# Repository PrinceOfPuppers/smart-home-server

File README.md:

# Smart Home Server
> A Full Smart Home System and Associated IOT Devices

- [DEVICES](#devices)
- [INSTALLATION](#installation)
  * [INSTRUCTIONS](#instructions)
- [ABOUT](#about)
  * [JOBS AND MACROS](#jobs-and-macros)
  * [DATASOURCES](#datasources)
- [PAGES](#pages)
  * [DASHBOARD](#dashboard)
  * [NOTE](#note)
  * [LCD](#lcd)
  * [REMOTE](#remote)
  * [SCHEDULE](#schedule)
  * [TRIGGER](#trigger)
  * [MACRO](#macro)
  * [GRAPH](#graph)

# DEVICES
Each device has its own `README`. Click the links to read more.

[ESP32 Air Quality Station](devices/esp32-air-quality-station/README.md) and [ESP Dashboard](devices/esp-dashboard/README.md):

<br clear="left"/>
<br clear="left"/>

[Main Case](devices/main-case/README.md) and [Arduino Blinds Controller](devices/arduino-blinds/README.md):

<br clear="left"/>
<br clear="left"/>

[Atmega16u2 Monitor](devices/atmega16u2-monitor/README.md)

<br clear="left"/>
<br clear="left"/>

[ESP Weather Station](devices/esp-weather-station/README.md) and [Arduino Modular Controller](devices/arduino-modular-controller/README.md):

<br clear="left"/>
<br clear="left"/>

# INSTALLATION
This section covers the installation of the central smart-home-server (hereto called "the server"). For a full parts list and physical assembly see: [Main Case Readme.md](devices/main-case/README.md)

The server runs RaspberryPi OS Lite, it has only been tested on a RaspberryPi 4B. I'd recommend using rpi-imager for creating the image as it lets you setup WiFi, SSH, etc, for an easier experience.

### Instructions
1) Flash an SD card with RaspberryPi OS Lite using rpi-imager, edit the settings to configure your user, WiFi, ssh, and other settings

2) Boot up the server and let it connect to wifi, in your router set a static IP address for the server

3) Reboot the server and connect to it over ssh

4) Ensure a USB stick is connected to the Pi and run: 

```
sudo apt install -y git && git clone https://github.com/PrinceOfPuppers/smart-home-server.git && cd smart-home-server && ./install.sh
```

5) The Installer will prompt you to select the usb stick from a list (will likley be the only one), after it is finished the server will be ready to go and accessable at its static ip address.

Note: The installer script enables read only file system, this makes the SD card readonly but still allows writing to the USB stick. You can disable this and re-enable it using `sudo raspi-config`

# ABOUT
The smart-home-server (hereto called "the server") is a device for collecting data and controlling IOT devices (hereto called "devices"). The server runs a full web interface for easy control on mobile or desktop.

The server's functionality is best understood through two categories, [Jobs and Macros](#jobs-and-macros) and [Datasources](#datasources).

## Jobs and Macros
Jobs are things the server can do, they include:
- Transmitting RF signals (for controlling RF outlets and relays)
- Sending HTTP requests
- Updating remote LCD Dashboard formats (see LCDs page)
- Running Job Macros
- Updating the server
- And more

Jobs can be organized into macros and setup to trigger in on RF signals, button presses on the server's case, or manually through the web page.

Jobs and macros can also be run using a scheduler (i.e. turn off the lights at 11pm) or can be triggered on conditions (i.e. turn on the humidifier whenever relative humidity is below 35%). See the [Schedule](#schedule) and [Trigger](#trigger) pages for more details.

Macros can also include delays and other macros.

### Example
Here is an example of a simple nighttime macro:

<br clear="left"/>
<br clear="left"/>

This macro turns off all the lights, turns off a loud air filter in the bedroom, waits for 8h30min, prevents you from oversleeping by turning on the bedroom light, and then turns everything in the bedroom off after 30 more minutes.

This macro could be hooked up to an RF button outside the bedroom to be run without having to open the web app (how I do it).

The macros like bedroom on/off would be replaced with single RF switching jobs, i.e.) `press bedroom ch: 1 on`, for the example macros where used so they could be labeled.

## Datasources
The server collects data from `datasources` with a set polling period. The data can then be used to:
- [Trigger](#trigger) server [Jobs](#jobs-and-macros) on conditions
- Displayed on the [Dashboard](#dashboard)
- Create [Graphs](#graph)
- Displayed on local and remote [LCDs](#lcd)

Examples of each Application:

<br clear="left"/>
<br clear="left"/>

<br clear="left"/>
<br clear="left"/>

Datasources can be added and changed on the `Datasources` tab if they fit into one of the existing types:
- `Forex`: currency converstion
- `Clock`: tells time
- `AQ`: air quality, temprature and humidity station
- `TempHumid`: temprature and humidity station
- `WeatherImage`: current weather with ascii art image
- `WeatherCurrent`: current weather simple representation
- `Forcast`: long term forcast chart
- `Errors`: log of errors in the smart home
- `JobLog`: log of run jobs
- `RfLog`: log of rf rx/tx
- `Version`: smart home version

New Datasource Form (left). Edit existing Datasource Form (right):

<br clear="left"/>
<br clear="left"/>

Each Datasource can be displayed in the Dashboard and provides values that can be consumed by Job Triggers, Graphs and LCDs

New types of Datasources can be added [here](smart_home_server/data_sources/datasourceTypes.py), by:
1) Creating a new subclass of `Datasource` (use an existing one as a base), Any required arguments should be annotated so they appear correctly in the `Datasource` form
2) Adding a `local` function which returns `{ 'str': '...', 'data':{...} }` where `str` is shown in dashboard and `data` contains the values used by triggers, graphs and etc (this function is polled to get the data).
3) Adding a `values` property which specifies what fields in `data` are relevant and what they should be called
4) Set a sane default polling period, although this is editable in the datasource form

# Pages

## Dashboard
A page for displaying desired datasources in an easy to read way, clicking on the name tag will refresh its information. Each datasource can be customized with buttons to hide its contents, colored name tags, buttons to make HTTP requests, and more.

<br clear="left"/>
<br clear="left"/>

## Note
A page to create, display and edit notes.

<br clear="left"/>
<br clear="left"/>

## LCD
A page to add and update local and [remote LCD](devices/esp-dashboard/README.md) dashboards.

LCDs display formatted text containing datasources, i.e. `{clock} 123` will be replaced with `02:03 PM 123` and will be updated every minute when the `{clock}` changes. This format is set on the LCD page, a list of all formats is provided under `Cheat Sheet`. Numbers can be rounded like so: `{temp:.0f}` for 0 decimal places or `{temp:.1f}` for 1 decimal place.

Each LCD has its own number (0 for local and 1 or more for remote), upon power up the LCDs will reach out to the server to connect, after which the server will send updates whenever the text changes.

<br clear="left"/>
<br clear="left"/>

## Remote
A page for using, adding and editing RF remotes. The server contains an RF receiver to copy existing remotes which can then hook into the server's [job system](#jobs-and-macros), in addition to directly using the copied remote from this page.

Each remote can be named, and additional buttons can be added using the forms at the bottom of the page.

<br clear="left"/>
<br clear="left"/>

## Schedule
A page for triggering [jobs and macros](#jobs-and-macros) repeatedly on a schedule. The server can be setup to run a job on an interval or at a specific time every day or week, for example turn on the Christmas lights at 5pm every day and turn them off at 5am every day.

<br clear="left"/>
<br clear="left"/>

## Trigger
A page for triggering [jobs and macros](#jobs-and-macros) on conditions involving [datasources](#dataSources). The server can be setup to run a job whenever a condition is met, for example whenever humidity is over 30%. comparisons can be made between two datasources as well, for example if you have 2 temperature sensors in different rooms, you can trigger a fan to turn on if room A temp is less than room B temp.

Note the condition is denounced, so it will only trigger once until the condition is no longer met. Using the humidity example, going below 30% will trigger the condition, but it will not trigger again until humidity goes above 30% and then below 30% again. This is to prevent spamming.

<br clear="left"/>
<br clear="left"/>

## Macro
A page for combining [jobs (and macros) into macros](#jobs-and-macros), macros can include jobs, delays and other macros to allow the easy triggering of complex tasks manually, on schedules or using the trigger system. See the [jobs and macro section](#jobs-and-macros) for examples.

<br clear="left"/>
<br clear="left"/>

## Graph
A page for creating plots of datasources over time. New graphs can be created by selecting a datasource, a color, and a time interval to plot over. All the plots are created server side and served as an image so they can be easily saved. Clicking on the plots name or refreshing the page will update it.

<br clear="left"/>
<br clear="left"/>

If an [Atmega16u2 Monitor](./devices/atmega16u2-monitor/README.md) is connected, you can press the `Monitor` button to push it to the screen where it will be updated whenever new data is added.

<br clear="left"/>
<br clear="left"/>

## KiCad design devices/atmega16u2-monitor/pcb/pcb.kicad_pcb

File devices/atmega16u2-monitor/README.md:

# Atmega16u2 Monitor
> An OLED and LCD USB Device for Displaying Graphs from smart-home-server

<br clear="left"/>
<br clear="left"/>

- [ABOUT](#about)
- [CREATION](#creation)
- [OPERATION](#operation)
- [TROUBLESHOOTING](#TROUBLESHOOTING)

# ABOUT
This device is a plug and play graph monitor for smart-home-server's data sources. When plugged in it will automatically connect to the server and start displaying whichever graph is selected in the UI (by pressing the `Monitor` button shown below). The image is updated whenever new data is added to the graph.

<br clear="left"/>
<br clear="left"/>

The device features a custom PCB built around the Atmega16u2

<br clear="left"/>
<br clear="left"/>

# CREATION

### PCB Creation and Assembly

JLCPCB was used for PCB creation and the majority of PCB assembly, files are provided in `./pcb/product`, these can be directly dropped into JLCPCB. The only things hand soldered are the USB connector, oscillator and debug header pin J5 (which is optional).

The schematic, PCB and components used can be edited in Kicad using file `./pcb/pcb.kicad_pro`, the JLCPCB files come from a plugin called `fabrication toolkit`.

<br clear="left"/>
<br clear="left"/>

### Display

I have tested with waveshare's OLED 1.5 inch display as well as their 1.8 inch LCD display. The type of display and its size are selected in `./firmware/config.h`. Wider displays may require increasing the number of `CHUNKS_PER_LINE` due to RAM limitations of the Atmega16u2.

The display's pins slot directly into the 8 pin port on the board. The pinout is `VCC, GND, DIN, CLK, CS, DC, RST, BL`. For OLED displays, `BL` is not used.

### Physical Assembly

3D printable cases for the 1.5 inch OLED and 1.8 inch LCD are provided under `./case/*.stl` as well as the openscad sources under `./case/*.scad`. Additional sizes can be added by editing `screenWidth` and `screenHeight` in the `.scad` files. Separate files exist for the OLED and LCD variants due to different pin locations.

The display is secured to the board using m2.5 standoffs as shown below, Note the OLED variant only uses one standoff due to its different form factor.

<br clear="left"/>
<br clear="left"/>

The screen is secured to the case using m2.5 screws, which screw into the standoffs (where present) or nuts. Nuts can also be used as spacers between the screen and case if desired.

<br clear="left"/>
<br clear="left"/>

### Firmware and Fuses

Fuses must be set on the Atmega16u2 for it to use the crystal resonator, these can be set by running:
```
./fuses.sh
```

The fuses should be `efuse: 0xF4`, `hfuse: 0xD9`, `lfuse 0xFF`. They can then be checked with:
```
./check_fuses.sh.sh
```

Fuses only need to be set once per device. Firmware can be uploaded by running the following.
```
./build.sh
```

The build relies [Hoodloader2](https://github.com/NicoHood/HoodLoader2) and [Hid Project](https://github.com/NicoHood/HID). The former makes the Atmega16u2 compatible with Arduino's build system and the latter is a library which manages the RawHID interface.

### UDEV and Testing
A UDEV rule must be added for Linux to know what to do with the USB device, smart-home-server does this automatically when installed. For local testing, a UDEV rule can be added by running the following script (once).
```
./udev.sh
```

After this, when the device is plugged in, it can be tested using the python script shown below. It will show a test graph and cycle through various line colors every 5 seconds.
```
python3 ./test.py
```

### Debugging
Uncomment `#define DEBUG_ENABLED` in `./firmware/config.h` and connect pin `J5` to the `RX` pin of a serial interface (I use a UART to USB adapter). This will give you serial debugging, several debug prints already exist in the code. Be mindful, `debug("test string");` stores the string `"test string"` in global RAM which can run out quickly on the Atmega16u2 and cause stack overflows. To give you more overhead, debug mode lowers the chunk size of the screen buffer.

Several macros exist for debug printing: `debug(x), debugln(x), debugS(x), debugSln(x)`. The `ln` variants print a newline after `x`, the `S` variants coerce `x` to a string before printing.

A debug LED is hooked up to pin `D6` (also known as pin `19`). It's free to use for debugging and is not accessed by anything else in the firmware.

# Operation
Once the device is assembled it can be plugged into the server, you can then select a graph to push to the screen. Only one graph can be shown at a time, the selected graph will have a grayed out button saying `Monitoring`, other graphs will have a colored button that says `Monitor`.

<br clear="left"/>
<br clear="left"/>

The graph updates whenever there is new data to display, the x axis is time relative to when it was last updated with time units displayed at the top.

<br clear="left"/>
<br clear="left"/>

# TROUBLESHOOTING

### USB not Connecting
The device should appear as a raw hid device under `/dev`, unplug it and run `ls /dev/hid*`, plug it back in and wait for a second, then run `ls /dev/hid*` again, a new device should appear.

You can also run the following command to check for USB add, bind, unbind and remove events.
```
udevadm monitor
```

If no device appears, it could be:
- device isn't plugged in properly
- firmware isn't flashed
- fuses aren't set correctly
- UDEV rule wasn't copied
- UDEV rules weren't reloaded
- hardware issues

Ensure the hardware is working using either serial debugging, or by blinking the debug led. You can also sniff USB traffic by connecting to the middle to pins on the USB adapter.

### Freezing
The device can freeze if undervolted (happens below 4v), some cheap USB splitters can cause this, if it occurs, try connecting directly to a USB port on your computer. The smart-home's USB ports have no issues. Freezing typically happens mid screen update.

### Slow Updating and USB Disconnects
Typically happens when the fuses are set incorrectly, check them with `./check_fuses.sh`. If the fuses are set properly check if `python3 ./test.py` changes color every 5 seconds. If so the timing is fine. If not, try re-running `./fuses.sh` (I've had say it succeeded, but the fuses remained unset). During normal operation, update speed is limited by chunk size which can be adjusted in `./firmware/config.h` by changing `#define CHUNKS_PER_LINE`. Fewer chunks is faster but uses more RAM and can lead to stack overflows.

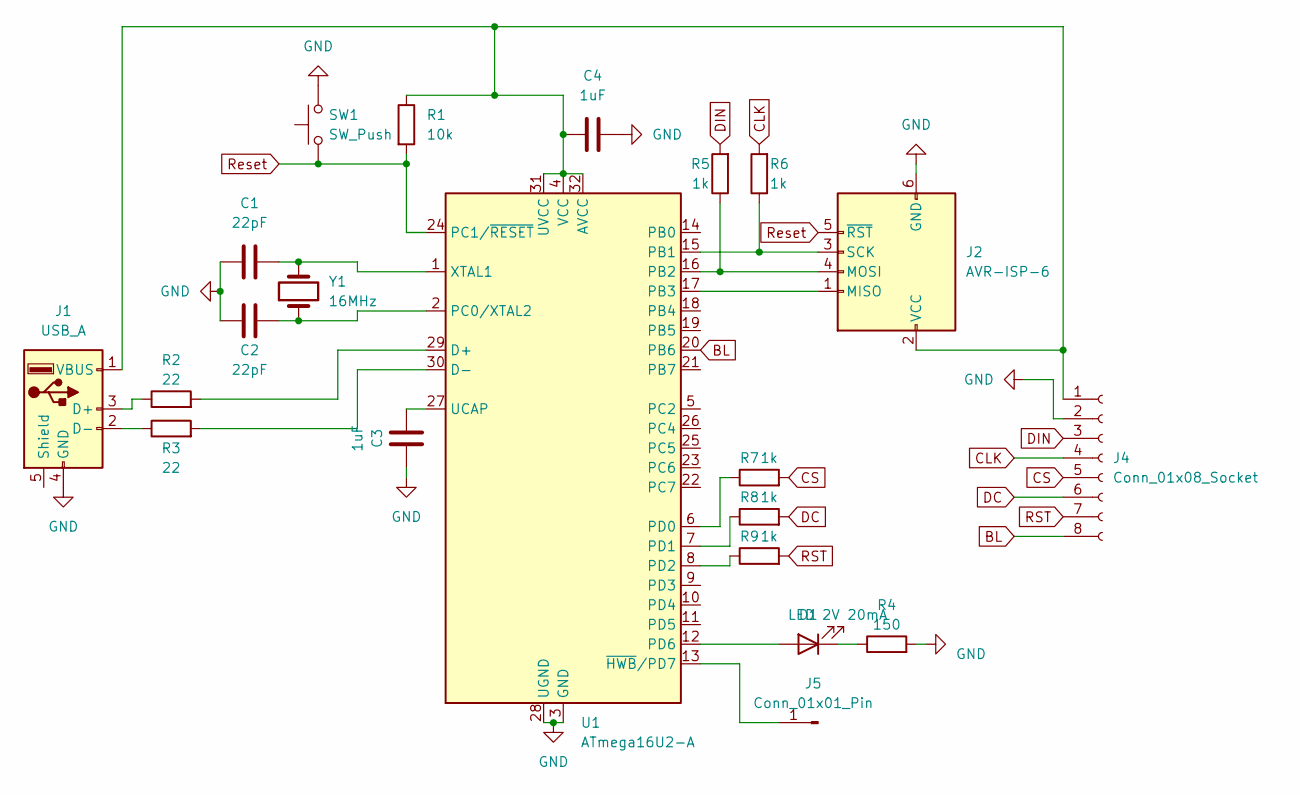
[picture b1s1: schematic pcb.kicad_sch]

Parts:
C1, C2: 22pF; C_0603_1608Metric
C3, C4: 1uF; C_0603_1608Metric
D1: LED 2V 20mA; LED_0603_1608Metric
J1: USB_A; USB_A_CNCTech_1001-011-01101_Horizontal
J2: AVR-ISP-6; PinHeader_2x03_P2.54mm_Horizontal
J4: Conn_01x08_Socket; PinSocket_1x08_P2.54mm_Vertical
J5: Conn_01x01_Pin; PinHeader_1x01_P2.54mm_Horizontal
R1: 10k; R_0603_1608Metric
R2, R3: 22; R_0603_1608Metric
R4: 150; R_0603_1608Metric
R5, R6, R7, R8, R9: 1k; R_0603_1608Metric
SW1: SW_Push; SW_Tactile_SPST_NO_Straight_CK_PTS636Sx25SMTRLFS
U1: ATmega16U2-A; TQFP-32_7x7mm_P0.8mm
Y1: 16MHz; Crystal_HC49-4H_Vertical

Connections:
BL: J4.8, U1.20 (PB6)
CLK: J4.4, R6.2
CS: J4.5, R7.2
DC: J4.6, R8.2
DIN: J4.3, R5.2
GND: C1.1, C2.1, C3.2, C4.2, J1.4 (GND), J2.6 (GND), J4.2, R4.2, SW1.2, U1.3 (GND), U1.28 (UGND)
unnamed: D1.2 (A), U1.12 (PD6)
unnamed: D1.1 (K), R4.1
unnamed: J1.3 (D+), R2.1
unnamed: J1.2 (D-), R3.1
unnamed: C4.1, J1.1 (VBUS), J2.2 (VCC), J4.1, R1.1, U1.4 (VCC), U1.31 (UVCC), U1.32 (AVCC)
unnamed: J2.1 (MISO), U1.17 (PB3)
unnamed: J2.4 (MOSI), R5.1, U1.16 (PB2)
unnamed: J2.3 (SCK), R6.1, U1.15 (PB1)
unnamed: J5.1, U1.13 (~HWB/PD7)
unnamed: R2.2, U1.29 (D+)
unnamed: R3.2, U1.30 (D-)
unnamed: C2.2, U1.2 (PC0/XTAL2), Y1.1
unnamed: R7.1, U1.6 (PD0)
unnamed: R8.1, U1.7 (PD1)
unnamed: R9.1, U1.8 (PD2)
unnamed: C3.1, U1.27 (UCAP)
unnamed: C1.2, U1.1 (XTAL1), Y1.2
RST: J4.7, R9.2
Reset: J2.5 (~RST), R1.2, SW1.1, U1.24 (PC1/~RESET)

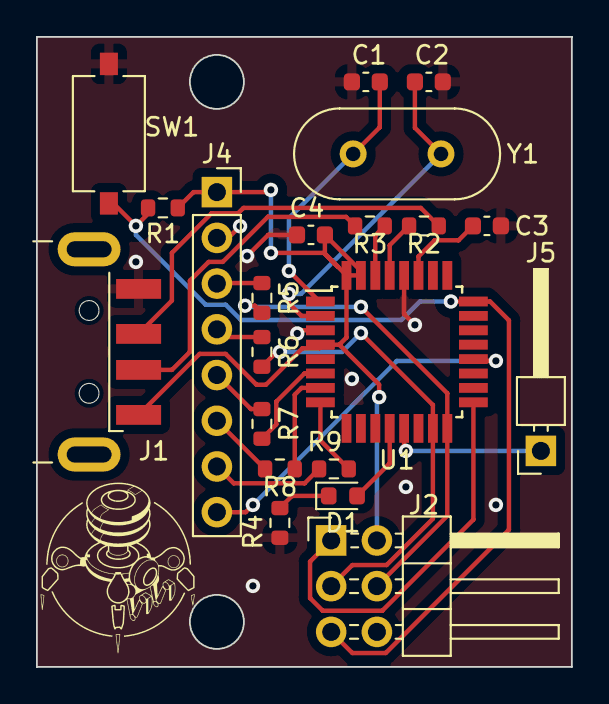
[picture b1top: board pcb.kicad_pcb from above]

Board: 2 copper layers, 29.7 x 35.0 mm, 21 parts (0 on the bottom side), 25 nets.

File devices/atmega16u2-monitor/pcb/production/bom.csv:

Designator,Footprint,Quantity,Value,LCSC Part #
"C1, C2",0603,2,22pF,
"C3, C4",0603,2,1uF,
D1,0603,1,LED 2V 20mA,
J1,USB_A_CNCTech_1001-011-01101_Horizontal,1,USB_A,
J2,PinHeader_2x03_P2.54mm_Horizontal,1,AVR-ISP-6,
J4,PinSocket_1x08_P2.54mm_Vertical,1,Conn_01x08_Socket,
J5,PinHeader_1x01_P2.54mm_Horizontal,1,Conn_01x01_Pin,
R1,0603,1,10k,
"R2, R3",0603,2,22,
R4,0603,1,150,
"R5, R6, R7, R8, R9",0603,5,1k,
SW1,SW_Tactile_SPST_NO_Straight_CK_PTS636Sx25SMTRLFS,1,SW_Push,
U1,TQFP-32_7x7mm_P0.8mm,1,ATmega16U2-A,
Y1,Crystal_HC49-4H_Vertical,1,16MHz,

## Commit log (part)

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2022-11-18 inital commit
2022-11-19 scheduler work
2022-11-19 project restructuring
2022-11-19 api seperation
2022-11-19 bugfixes
2022-11-19 demo site hookup
2022-11-20 rf tranmitter setup
2022-11-20 basic web interface for rf remote
2022-11-21 schedule frontend wip
2022-11-21 schedule frontend bugfixes
2022-11-21 removed hovor on mobile
2022-11-22 bugfixes and layout improvements
2022-11-22 layout changes
2022-11-22 beautification
2022-11-22 more bugfixes
2022-11-22 removed nobr tags, name updating, bugfixes
2022-11-22 small graphical improvements
2022-11-23 api directory structure changes
2022-11-23 additional dashboard elements
2022-11-23 additional sanitization
2022-11-24 lcd wip
2022-11-25 dashboard and lcd improvements
2022-11-25 dht sensor and general improvments
2022-11-25 api changes
2022-11-26 changed data system
2022-11-26 data sources cache
2022-11-27 trigger page wip
2022-11-27 trigger page wip 2
2022-11-27 trigger frontend done
2022-11-28 trigger bugfixes
2022-12-05 job system improvements and change lcd text job
2022-12-05 redirect index to dashboard
2022-12-05 lcd bugfixes
2022-12-06 setup scripts
2022-12-07 deployment bugfixes
2022-12-07 fixed submit form issues
2022-12-09 fixed deployment issues
2022-12-10 workarounds for bugs in wttr.in, moved presser to seperate process
2022-12-10 error system
2022-12-10 code cleanup
2022-12-10 partial lcd update jobs
2022-12-11 inital wip
2022-12-12 websock wip
2022-12-12 websocket robust frontend reconnecting
2022-12-12 fixed more with websockets
2022-12-12 replaced waitress with gevent
2022-12-13 removed websockets for performance reasons
2022-12-13 small fixes
2022-12-13 fixed bug with getCurrentWeather, made polling toggleable in code
2022-12-16 small bugfixes
2022-12-16 auto update on startup
2022-12-16 fixed missing fi in install script
2022-12-16 added missing then to install script
2022-12-18 changes to auto update system
2022-12-18 fixed typo
2022-12-19 dht powercycling
2022-12-19 fixed frontend time string
2022-12-21 better caching system
2022-12-22 version string in dashboard
2022-12-24 fixed bug with pigpiod
2022-12-27 added stacktraces to exceptions
2022-12-27 fixed deadlock in caching on function exception
2022-12-28 added update to install script
2022-12-30 multi remote system
2022-12-30 request timeout
2022-12-31 note system
2022-12-31 macro system inital work
2022-12-31 note newline bugfixes
2023-01-01 reactive buttons
2023-01-01 removed repatition
2023-01-01 macro wip 2
2023-01-01 macro wip 3
2023-01-01 macro wip 4
2023-01-02 macro bugfixes
2023-01-02 improved macro visuals
2023-01-02 visual improvments and removed repititions
2023-01-02 added missing characters to font
2023-01-02 fixed issue with trigger enable/disable system
2023-01-02 dethreaded trigger manager
2023-01-02 added reboot job
2023-01-02 macro renaming and small refactoring
2023-01-02 style improvements
2023-01-02 reboot fixes and style changes
2023-01-03 refactoring
2023-01-03 note refactor
2023-01-03 renamed threads to handlers
2023-01-03 scheduler error system refactor
2023-01-03 made errorhandling and data validation/sanitization more consistant across parts of the api
2023-01-04 added macro to job system
2023-01-04 systemd start after timesync
2023-01-07 after time-sync.target
2023-01-08 skip/cancel macro delay
2023-01-08 removed weather from dashboard due to inaccuracies
2023-01-08 changed order of delay time inputs to hh/mm/ss
2023-01-08 reboot delay timer
2023-01-13 presser process priority
2023-02-06 delayed scheduler loading to account for system time issues on startup
2023-02-24 removing press delay
2023-03-06 api wip
2023-03-08 gui wip
2023-03-08 backend wip
2023-03-08 more frontend wip
2023-03-09 bugfixes and wip
2023-03-09 bugfixes:
2023-03-09 cleanup
2023-03-09 removed deadlock
2023-03-09 preformance improvements
2023-03-09 re added presser thread
2023-03-10 bugfixes and refactoring
2023-03-10 minor graphical tweak and version bump
2023-03-11 software update job
2023-03-14 offset frontend remote channels by 1
2023-03-14 fixed update job
2023-03-14 auto update test
2023-07-08 rf runner thread
2023-07-08 rf macro api
2023-07-09 rf macro frontend work and backend bugfixes
2023-07-09 adjusted rf macro constants
2023-07-10 rf log and hideable elements in dashboard
2023-07-10 dashboard button system and clearable logs
2023-07-10 bumped version number
2023-07-10 minor bugfix
2023-07-10 fixed bug with missing macro id
2023-07-11 more dashboard automation
2023-07-21 renamed
2023-07-23 restructured project
2023-07-23 motion sensor code
2023-07-23 light sensor intial code
2023-07-24 bugfix
2023-08-05 light sensor fixes and debugging
2023-08-07 motion sensor improvement
2023-08-11 potentiometer servo adjustment and field runnable tests
2023-08-11 readme
2023-08-11 Fixed readme format errors
2023-08-11 readme grammer and formatting
2023-08-12 updated servo-invert and servo adjustment range
2023-08-12 updated readme section about servo invert
2023-08-16 tx trigger
2023-08-16 power trigger
2023-08-17 fixed power trigger schematic
2023-11-25 fixed spelling mistake
2023-11-25 fixed issue with return in getBME
2023-11-25 indoor climate rounding
2023-11-25 remote renaming
2023-11-25 macro controls refresh page
2023-11-26 outdoor weather server integration
2023-11-26 ui changes
2023-12-01 made lcd dimensions configurable
2023-12-01 case model
2023-12-02 updated case
2023-12-02 wttrin bugfix
2023-12-02 more wttrin bugfixes
2023-12-03 subscribe manager none error
2023-12-09 updated case model
2023-12-09 added model for weather station case
2023-12-09 indoor weather server added
2023-12-09 added print chamber temp humid station
2023-12-09 fixed issue with caching
2023-12-11 added weather station files
2023-12-11 removed gitignore from subdir
2023-12-11 added devices subdir
2023-12-12 dashboard device inital code
2023-12-14 forcast time indicator
2023-12-23 dashboard case model
2023-12-26 updated dashboard case model
2023-12-28 remote dashboard server code wip
2023-12-29 remote dashboard server code wip 2
2023-12-29 remote dashboard server code wip 3
2023-12-30 remote dashboard api
2023-12-30 inital frontend work for remote dashboard
2023-12-30 remote dashboard frontend wip
2023-12-30 remote dashboard frontend working
2023-12-31 switched over remote dashboard to use TCP instead of UDP
2024-01-02 fix fmt change inducing reconnect
2024-01-02 fixed issue with tcp ports never timing out
2024-01-03 fixed issue with lcd buffer being too small
2024-01-04 lcd backlight toggling
2024-01-04 udp multiple attempts
2024-01-08 added indicator on lcds page for active lcds
2024-01-08 added tcp keepalive, hardware timer watchdog and wifi disconnect handler to esp dashboard
2024-01-10 weather station alternative case
2024-01-10 set esp dashboard hostname
2024-01-10 usb case fix
2024-01-11 added additional weather station
2024-02-04 pms sensor sleep wake cycle
2024-02-05 fixed compile errors
2024-02-05 restart on disconnect
2024-02-05 added data transmission code
2024-02-05 bugfixes and full testing
2024-02-11 s8 calibration and bugfixes
2024-02-12 air quality station case wip
2024-02-13 air quality station case
2024-02-14 air quality station case update
2024-02-14 air quality station bugfixes and docs update
2024-02-14 air quality station images
2024-02-14 air quality station updated readme
2024-02-14 added smart-home-server support
2024-02-15 redesigned error system
2024-02-15 manual error clearing
2024-02-15 added readme for esp-dashboard device
2024-02-15 updated readme for esp-dashboard device
2024-02-17 added readme for esp-weather-station
2024-02-17 reverted max-height to height in readmes
2024-02-18 rounding support in formatter
2024-02-18 bumped lcd api maxLength
2024-02-18 bumped verion number
2024-02-19 inital graphs commit
2024-02-20 graph api
2024-02-20 inital graph integration
2024-02-20 more graph integration
2024-02-20 removed graph names and updating
2024-02-20 graph colors
2024-02-21 made button layout tighter
2024-02-21 fixed small text on macro page
2024-02-21 updated dependancies and version bump
2024-02-21 fixed button color
2024-02-21 additional errors
2024-02-22 created jinja macro for topnav
2024-02-26 readme wip
2024-02-26 bugfixes and ui changes
2024-02-28 more readme wip
2024-02-28 readme first draft
2024-02-28 fixed readme images
2024-02-28 readme spelling fixes
2024-02-29 readme proofreading
2024-03-22 blinds scad files added
2024-03-22 added chain gear model and fixed imports
2024-03-27 mechanical design updates and debug mode
2024-04-12 fixed incorrect clock type bug
2024-04-13 added infield rx programming
2024-04-14 added readme for arduino blinds
2024-04-14 updated main readme
2024-04-14 spelling corrections
2024-04-20 inital commit, working fuses and build system
2024-04-22 usb udev rule, simple raw hid echo test
2024-04-25 minimal working example
2024-04-25 direct port manipulation for performance improvement
2024-04-26 device state machine
2024-04-27 device driver auto connect, and device performance improvements
2024-04-27 incremental progress
2024-04-28 protocol reliability
2024-04-28 smart home integration progress
2024-04-28 smart home integration progress 2
2024-04-28 smart home integration done
2024-05-01 atmega16u2-monitor pcb
2024-05-05 renamed arduino light switcher to arduino modular controller
2024-05-12 created light trigger for arduino modular control system, minor rx tx tweaks
2024-05-18 monitor shroud
2024-05-22 small tweaks and added dependancies
2024-05-23 changed monitor connect disconnect logic
2024-05-23 graph formatting and version bump
2024-05-23 installer script update and small tweak
2024-05-23 install/uninstall script changes
2024-05-23 install/uninstall script fixes
2024-05-23 removed dht module, switched over gpio driver
2024-05-24 added support for oled modules
2024-05-28 oled case
2024-05-29 added monitor photos to main readme
2024-05-29 minor readme tweaks
2024-05-30 readme proofreading and arduino-blinds chain gear redesign
2024-05-30 arduino modular controller action repeat system
2024-06-01 added delay to graph runtime startup to allow linux clock to stabalize
2025-12-09 datasource save/load, and schema
2025-12-09 made weather info configurable
2025-12-09 reorganization and fixes
2025-12-09 todos
2025-12-10 form from schema
2025-12-11 code reuse and datasource form parsing
2025-12-12 datasource frontend working, api endpoint created
2025-12-14 annotation system
2025-12-14 from/to json methods
2025-12-14 ignore missing annotations for schemas
2025-12-15 fixes
2025-12-15 working annotation based schema
2025-12-15 ui hints system
2025-12-16 auto form required fields
2025-12-16 data sanitization system
2025-12-17 wip datasourceInterface, form prepopulation
2025-12-17 made datasourceTypes frozen
2025-12-17 working datasource append, fixed datasource consumers
2025-12-24 datasource api nearly finished
2025-12-24 better datasource form styling
2025-12-27 datasource reordering
2025-12-27 initial job dataclass structure
2025-12-27 ported temp/humid sensor to pio
2025-12-28 ported esp32 air quality station to pio
2025-12-28 wip port of esp-dashbord from arduino to pio
2025-12-28 fixed forex datasource
2025-12-28 datasource styling
2025-12-28 made existing datasources hideable
2025-12-29 pigpio replaced with gpiozero, installer script updates, readme updates
2025-12-29 improved usb drive selection in installer script
2025-12-29 safer pathing in installer script
2025-12-29 edited usb mount fstab entry
2025-12-29 more installer script fixes
2025-12-29 added guard against incorrect usb file systems in installer script
2025-12-29 made installer script work with any usb ftype
2025-12-29 installer tweaks
2025-12-30 made systemd bin work with venv
2025-12-30 systemd service changes and gpiozero removal
2025-12-30 explicit starting of gpio
2025-12-30 made overlayfs not effect external drives
2025-12-31 switched to rpi-rf-gpiod and gpiozero
2026-01-01 integrated rpi_rf directly to avoid issue with RPi.GPIO dependancy
2026-01-01 added toggle for i2c bme280 to constants
2026-01-18 working camera firmware
2026-01-19 added pcb holder to case
2026-01-19 added pcb holder post to case
2026-01-19 updated case stl
2026-01-20 small case and code tweaks
2026-01-20 remove abs from rpi_rf that was breaking it
